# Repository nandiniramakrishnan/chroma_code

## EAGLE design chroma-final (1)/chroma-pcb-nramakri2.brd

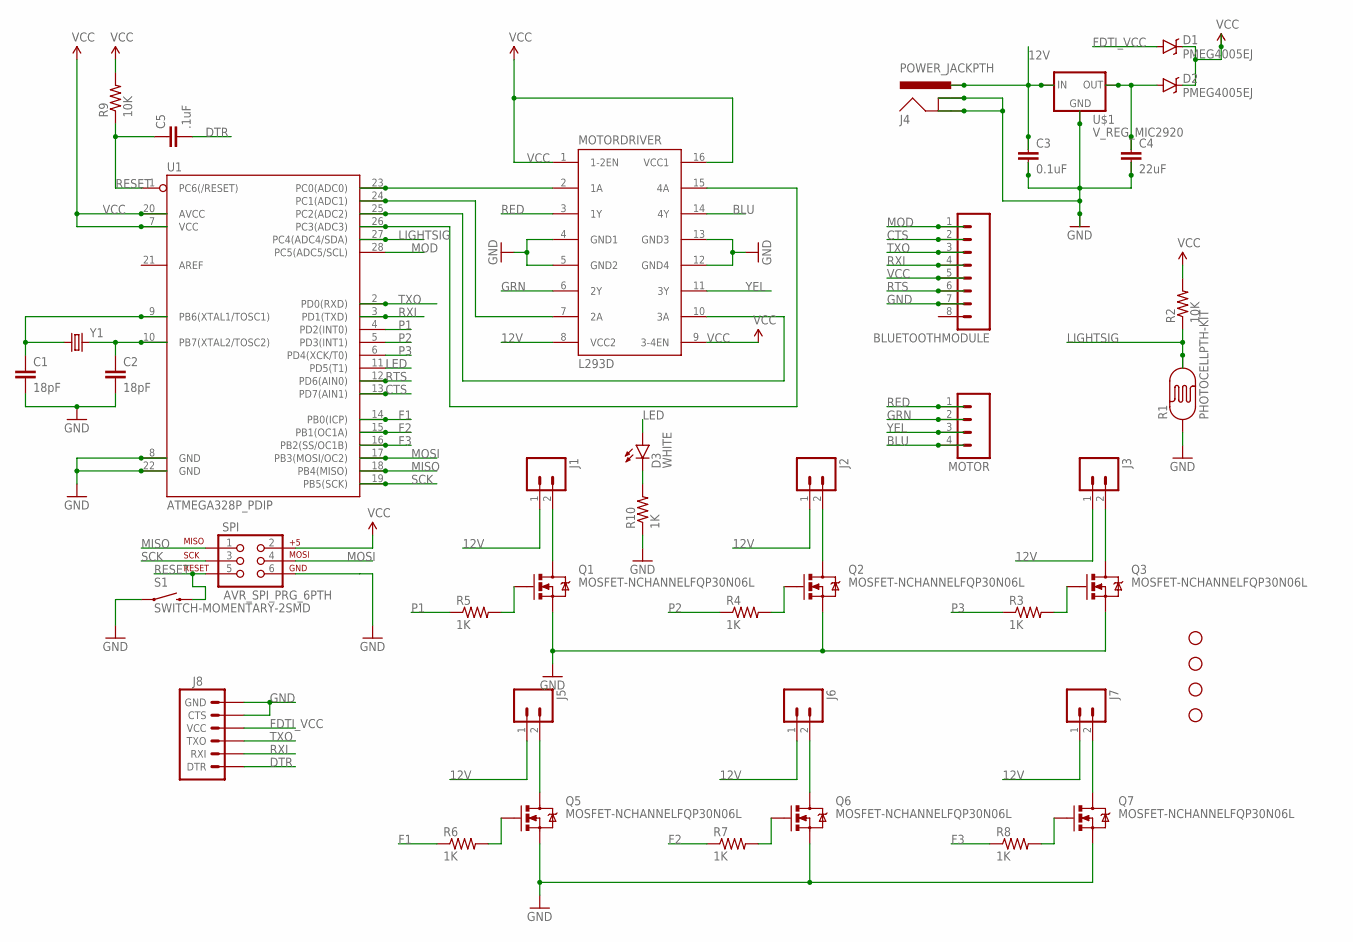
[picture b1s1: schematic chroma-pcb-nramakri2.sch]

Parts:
BLUETOOTHMODULE: M08; 1X08_ROUND
C1, C2: 18pF; 1206
C3: 0.1uF; 1206
C4: 22uF; 1206
C5: .1uF; 1206
D1, D2: PMEG4005EJ; SOD-323
D3: WHITE; LED5MM
H1, H2, H3, H4: STAND-OFF
J1, J2, J3, J5, J6, J7: M023.5MM; SCREWTERMINAL-3.5MM-2
J4: POWER_JACKPTH; POWER_JACK_PTH
J8: ARDUINO_SERIAL_PROGRAMPTH; 1X06
MOTOR: M04PTH; 1X04
MOTORDRIVER: L293D; DIL16
Q1, Q2, Q3, Q5, Q6, Q7: MOSFET-NCHANNELFQP30N06L; TO220V
R1: PHOTOCELLPTH-KIT; PHOTOCELL-KIT
R2, R9: 10K; 1206
R3, R4, R5, R6, R7, R8, R10: 1K; 1206
S1: SWITCH-MOMENTARY-2SMD; TACTILE-SWITCH-SMD
SPI: AVR_SPI_PRG_6PTH; 2X3
U1: ATMEGA328P_PDIP; DIL28-3
U$1: V_REG_MIC2920; SOT223
Y1: CRYSTALTXC-7A; CRYSTAL-TXC-7A

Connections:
12V: C3.1, J1.1, J2.1, J3.1, J4.PWR, J5.1, J6.1, J7.1, MOTORDRIVER.8 (VCC2), U$1.1 (IN)
BLU: MOTOR.4, MOTORDRIVER.14 (4Y)
CTS: BLUETOOTHMODULE.2, U1.13 (PD7(AIN1))
DTR: C5.2, J8.1 (DTR)
F1: R6.1, U1.14 (PB0(ICP))
F2: R7.1, U1.15 (PB1(OC1A))
F3: R8.1, U1.16 (PB2(SS/OC1B))
FDTI_VCC: D1.A, J8.4 (VCC)
GND: BLUETOOTHMODULE.7, C1.2, C2.2, C3.2, C4.2, J4.GND, J4.GNDBREAK, J8.5 (CTS), J8.6 (GND), MOTORDRIVER.4 (GND1), MOTORDRIVER.5 (GND2), MOTORDRIVER.12 (GND4), MOTORDRIVER.13 (GND3), Q1.3 (S), Q2.3 (S), Q3.3 (S), Q5.3 (S), Q6.3 (S), Q7.3 (S), R1.1, R10.1, S1.1, SPI.6, U1.8 (GND), U1.22 (GND), U$1.2 (GND)
GRN: MOTOR.2, MOTORDRIVER.6 (2Y)
LED: D3.A, U1.11 (PD5(T1))
LIGHTSIG: R1.2, R2.1, U1.27 (PC4(ADC4/SDA))
MISO: SPI.1, U1.18 (PB4(MISO))
MOD: BLUETOOTHMODULE.1, U1.28 (PC5(ADC5/SCL))
MOSI: SPI.4, U1.17 (PB3(MOSI/OC2))
unnamed: MOTORDRIVER.2 (1A), U1.23 (PC0(ADC0))
unnamed: MOTORDRIVER.7 (2A), U1.24 (PC1(ADC1))
unnamed: MOTORDRIVER.10 (3A), U1.25 (PC2(ADC2))
unnamed: MOTORDRIVER.15 (4A), U1.26 (PC3(ADC3))
unnamed: D3.K (C), R10.2
unnamed: C2.1, U1.10 (PB7(XTAL2/TOSC2)), Y1.P$2 (2)
unnamed: Q1.1 (G), R5.2
unnamed: C4.1, D2.A, U$1.3 (OUT)
unnamed: Q5.1 (G), R6.2
unnamed: Q6.1 (G), R7.2
unnamed: Q7.1 (G), R8.2
unnamed: C1.1, U1.9 (PB6(XTAL1/TOSC1)), Y1.P$1 (1)
unnamed: Q3.1 (G), R3.2
unnamed: Q2.1 (G), R4.2
unnamed: J5.2, Q5.2 (D)
unnamed: J1.2, Q1.2 (D)
unnamed: J2.2, Q2.2 (D)
unnamed: J3.2, Q3.2 (D)
unnamed: J6.2, Q6.2 (D)
unnamed: J7.2, Q7.2 (D)
P1: R5.1, U1.4 (PD2(INT0))
P2: R4.1, U1.5 (PD3(INT1))
P3: R3.1, U1.6 (PD4(XCK/T0))
RED: MOTOR.1, MOTORDRIVER.3 (1Y)
RESET: C5.1, R9.1, S1.3 (2), SPI.5, U1.1 (PC6(/RESET))
RTS: BLUETOOTHMODULE.6, U1.12 (PD6(AIN0))
RXI: BLUETOOTHMODULE.4, J8.2 (RXI), U1.3 (PD1(TXD))
SCK: SPI.3, U1.19 (PB5(SCK))
TXO: BLUETOOTHMODULE.3, J8.3 (TXO), U1.2 (PD0(RXD))
VCC: BLUETOOTHMODULE.5, D1.C, D2.C, MOTORDRIVER.1 (1-2EN), MOTORDRIVER.9 (3-4EN), MOTORDRIVER.16 (VCC1), R2.2, R9.2, SPI.2, U1.7 (VCC), U1.20 (AVCC)
YEL: MOTOR.3, MOTORDRIVER.11 (3Y)

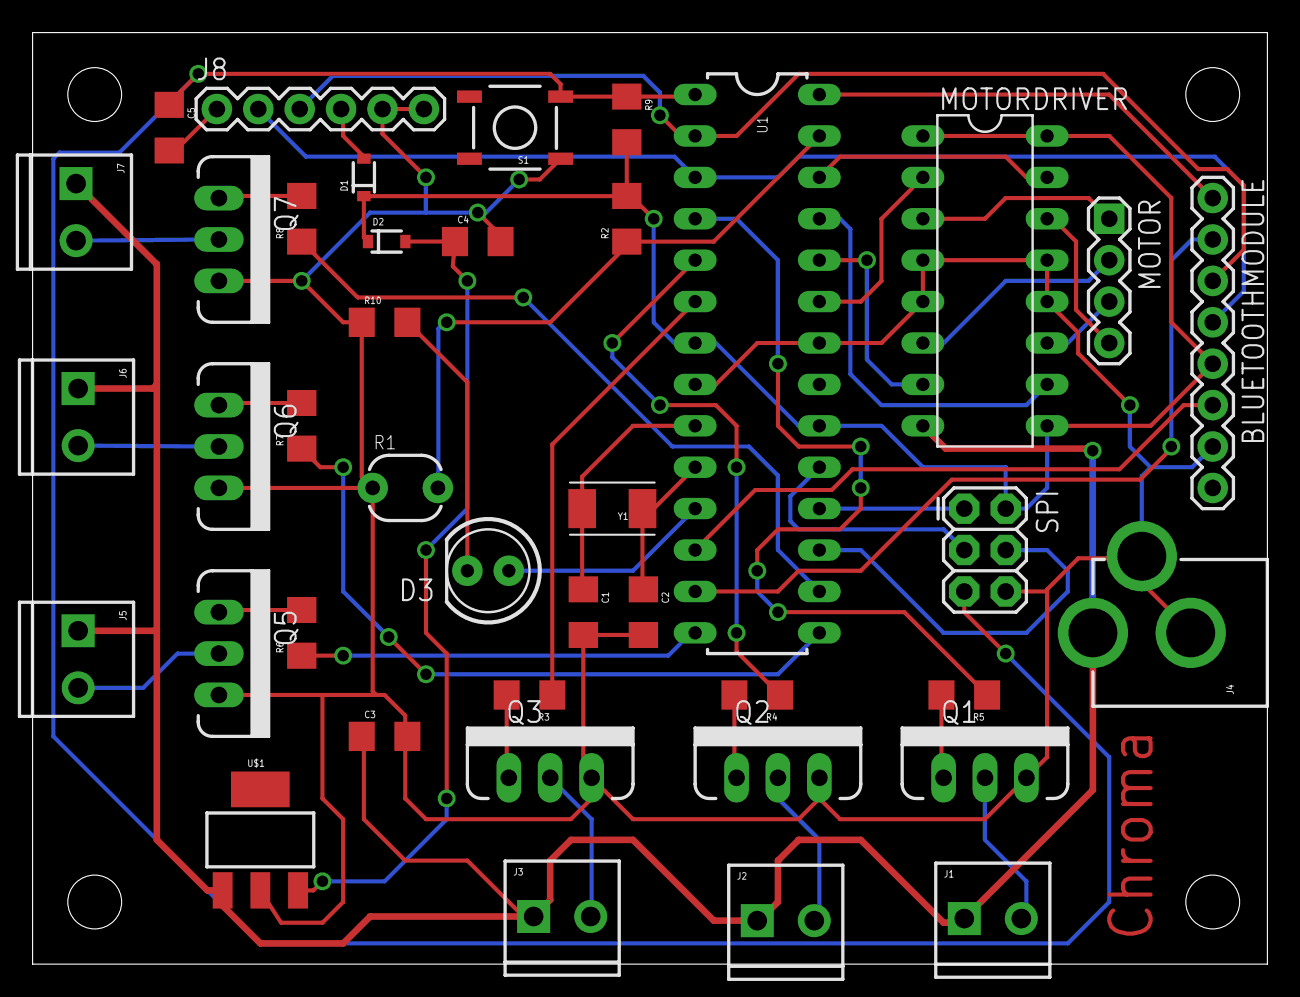
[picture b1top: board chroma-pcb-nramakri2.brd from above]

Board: 2 copper layers, 75.7 x 57.1 mm, 44 parts (0 on the bottom side), 46 nets.

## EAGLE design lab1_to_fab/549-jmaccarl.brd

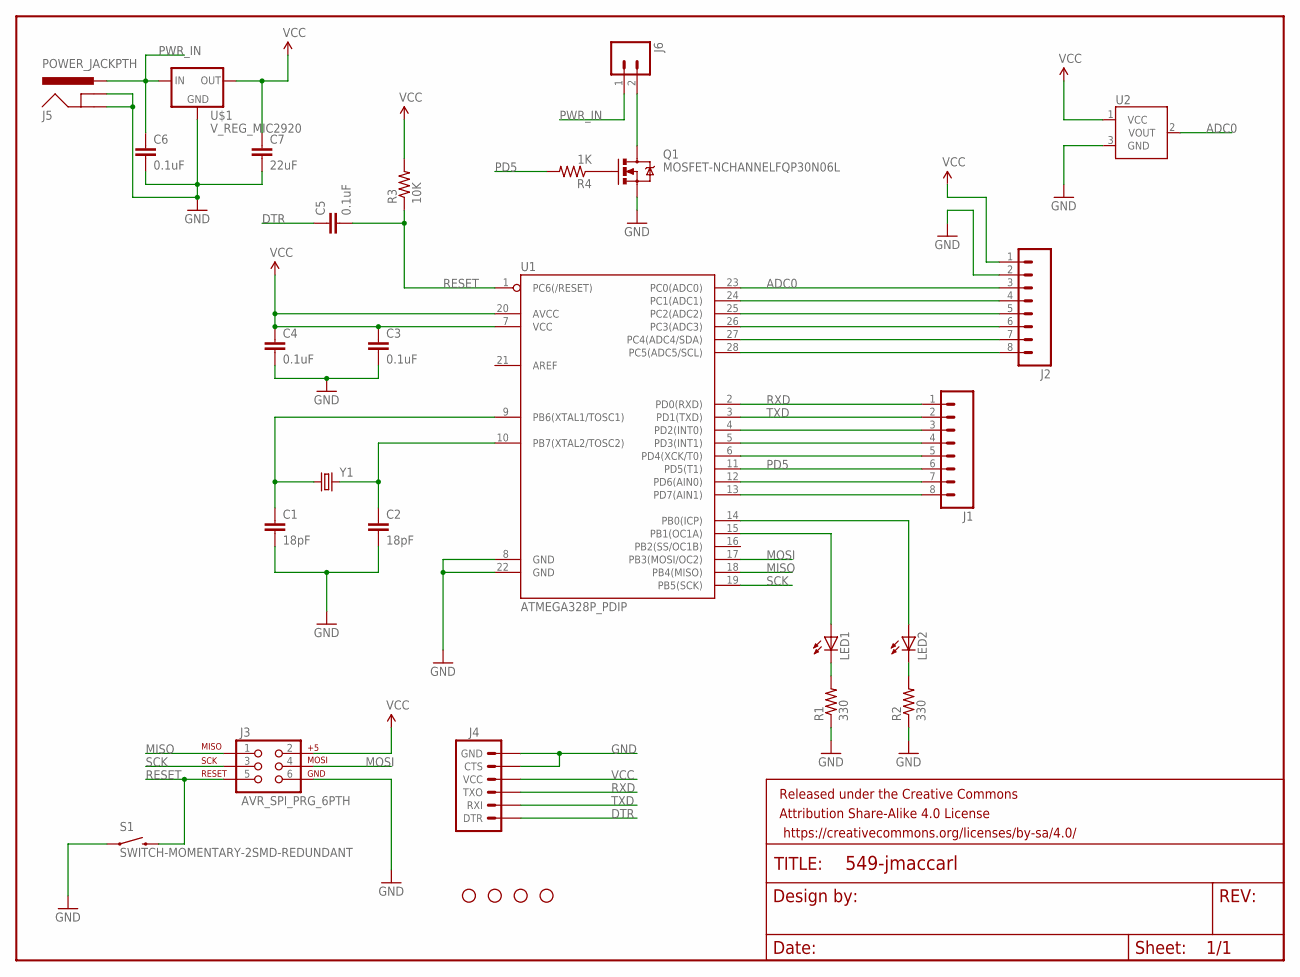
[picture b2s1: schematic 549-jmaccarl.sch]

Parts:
C1, C2: 18pF; 1206
C3, C4, C5, C6: 0.1uF; 1206
C7: 22uF; 1206
FRAME1: FRAME-LETTER; CREATIVE_COMMONS
H1, H2, H3, H4: STAND-OFF
J1, J2: M08LOCK; 1X08_LOCK
J3: AVR_SPI_PRG_6PTH; 2X3
J4: ARDUINO_SERIAL_PROGRAMPTH; 1X06
J5: POWER_JACKPTH; POWER_JACK_PTH
J6: M025MM; SCREWTERMINAL-5MM-2
LED1, LED2: LED1206; LED-1206
Q1: MOSFET-NCHANNELFQP30N06L; TO220V
R1, R2: 330; 1206
R3: 10K; 1206
R4: 1K; 1206
S1: SWITCH-MOMENTARY-2SMD-REDUNDANT; TACTILE-SWITCH-SMD
U1: ATMEGA328P_PDIP; DIL28-3
U2: TMP36GT9; TO-92
U$1: V_REG_MIC2920; SOT223
Y1: CRYSTALTXC-7A; CRYSTAL-TXC-7A

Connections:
ADC0: J2.3, U1.23 (PC0(ADC0)), U2.2 (VOUT)
DTR: C5.1, J4.1 (DTR)
GND: C1.2, C2.2, C3.2, C4.2, C6.2, C7.2, J2.2, J3.6, J4.5 (CTS), J4.6 (GND), J5.GND, J5.GNDBREAK, Q1.3 (S), R1.1, R2.1, S1.1, S1.2 (1), U1.8 (GND), U1.22 (GND), U2.3 (GND), U$1.2 (GND)
MISO: J3.1, U1.18 (PB4(MISO))
MOSI: J3.4, U1.17 (PB3(MOSI/OC2))
unnamed: LED1.A, U1.15 (PB1(OC1A))
unnamed: LED1.C, R1.2
unnamed: LED2.A, U1.14 (PB0(ICP))
unnamed: LED2.C, R2.2
unnamed: J1.8, U1.13 (PD7(AIN1))
unnamed: J1.7, U1.12 (PD6(AIN0))
unnamed: J6.2, Q1.2 (D)
unnamed: J1.5, U1.6 (PD4(XCK/T0))
unnamed: J1.4, U1.5 (PD3(INT1))
unnamed: J1.3, U1.4 (PD2(INT0))
unnamed: Q1.1 (G), R4.1
unnamed: J2.8, U1.28 (PC5(ADC5/SCL))
unnamed: J2.7, U1.27 (PC4(ADC4/SDA))
unnamed: J2.6, U1.26 (PC3(ADC3))
unnamed: J2.5, U1.25 (PC2(ADC2))
unnamed: J2.4, U1.24 (PC1(ADC1))
unnamed: C2.1, U1.10 (PB7(XTAL2/TOSC2)), Y1.P$2 (2)
unnamed: C1.1, U1.9 (PB6(XTAL1/TOSC1)), Y1.P$1 (1)
PD5: J1.6, R4.2, U1.11 (PD5(T1))
PWR_IN: C6.1, J5.PWR, J6.1, U$1.1 (IN)
RESET: C5.2, J3.5, R3.1, S1.3 (2), S1.4 (2), U1.1 (PC6(/RESET))
RXD: J1.1, J4.3 (TXO), U1.2 (PD0(RXD))
SCK: J3.3, U1.19 (PB5(SCK))
TXD: J1.2, J4.2 (RXI), U1.3 (PD1(TXD))
VCC: C3.1, C4.1, C7.1, J2.1, J3.2, J4.4 (VCC), R3.2, U1.7 (VCC), U1.20 (AVCC), U2.1 (VCC), U$1.3 (OUT)

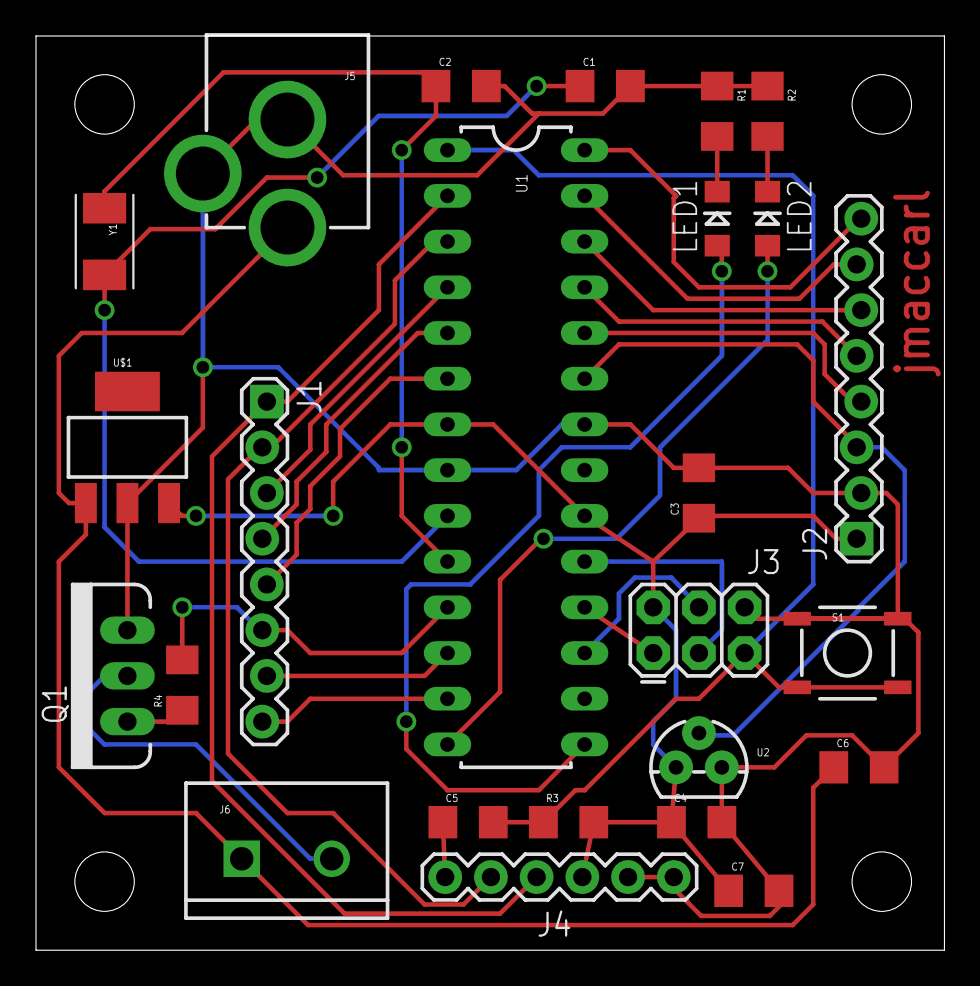
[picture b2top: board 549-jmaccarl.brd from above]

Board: 2 copper layers, 50.5 x 50.8 mm, 30 parts (0 on the bottom side), 30 nets.

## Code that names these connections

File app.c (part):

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 * Description:
 *
 * Pin functions:
 * Fuel injectors (PWM) -  PD6, PB1, PB2
 * Pumps - PD2, PD3, PD4
 * LED - PD5
 * Photo sensor - PC4
 * Motor - PC0, PC1, PC2, PC3
 *
 */

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}

/* Methods to turn each pump on */
void pump1_on() {             // PD2
  PORTD |= 0x40;              // 0000 0100
}

void pump2_on() {             // PD3
  PORTD |= 0x08;              // 0000 1000
}

void pump3_on() {             // PD4
  PORTD |= 0x10;              // 0001 0000
}

/* Methods to turn each pump off */
void pump1_off() {            // PD2     
  PORTD &= 0xFD;              // 1111 1011
}

void pump2_off() {            // PD3
  PORTD &= 0xF7;              // 1111 0111
}

void pump3_off() {            // PD4
  PORTD &= 0xEF;              // 1110 1111
}

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
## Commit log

2016-03-27 Tutorial from online
2016-03-27 added UART to laptop code
2016-03-27 Tried using two baud rates in same code. This is wrong.
2016-03-30 a change i dont remember
2016-03-31 latest code
2016-04-02 Added code to test PWM and the main app code
2016-04-02 Pushed working USART barebones code
2016-04-03 Fixed bug: Changed pwm init from timer 2 to 0. Added starter timer testing code
2016-04-03 Removed return values of write and read functions in UART
2016-04-04 added motor test from old repo
2016-04-09 Added lab 2 files, including bootloader
2016-04-09 Added Chroma eagle project
2016-04-09 Committing remaining test folders
2016-04-09 Added motor_pwm
2016-04-09 remove tracking old timer files
2016-04-13 attempt to get all three to spray at once
2016-04-13 fixed bugs. to test
2016-04-18 latest changes 4/17
2016-04-18 Changed interval to a MACRO
2016-04-18 Added more comments. Added period check in receive interrupt. Removed disable interrupt (commented)
2016-04-18 fixed bug where magentaval was being set before magenta. also changed type of u8data in bufferwrite declaration
2016-04-18 changed order to mcy and add more timer settings
2016-04-18 made reset_ptinter smaller by moving some methods to main. removed resetting of some variables. problem with prev commit - reset not getting called. motor not turning off (why??)
2016-04-18 added get colours. moved colour writing code to main
2016-04-18 MVP THIS WORKSSSSS
2016-04-22 Added print complete and substrate detection trasmit messages. Added ADC code

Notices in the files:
parts and their libraries:
SparkFun-Connectors: Licensing: Creative Commons ShareAlike 4.0 International - https://creativecommons.org/licenses/by-sa/4.0
SparkFun-Aesthetics: Released under the Creative Commons Attribution Share-Alike 4.0 License
SparkFun-Aesthetics: https://creativecommons.org/licenses/by-sa/4.0
